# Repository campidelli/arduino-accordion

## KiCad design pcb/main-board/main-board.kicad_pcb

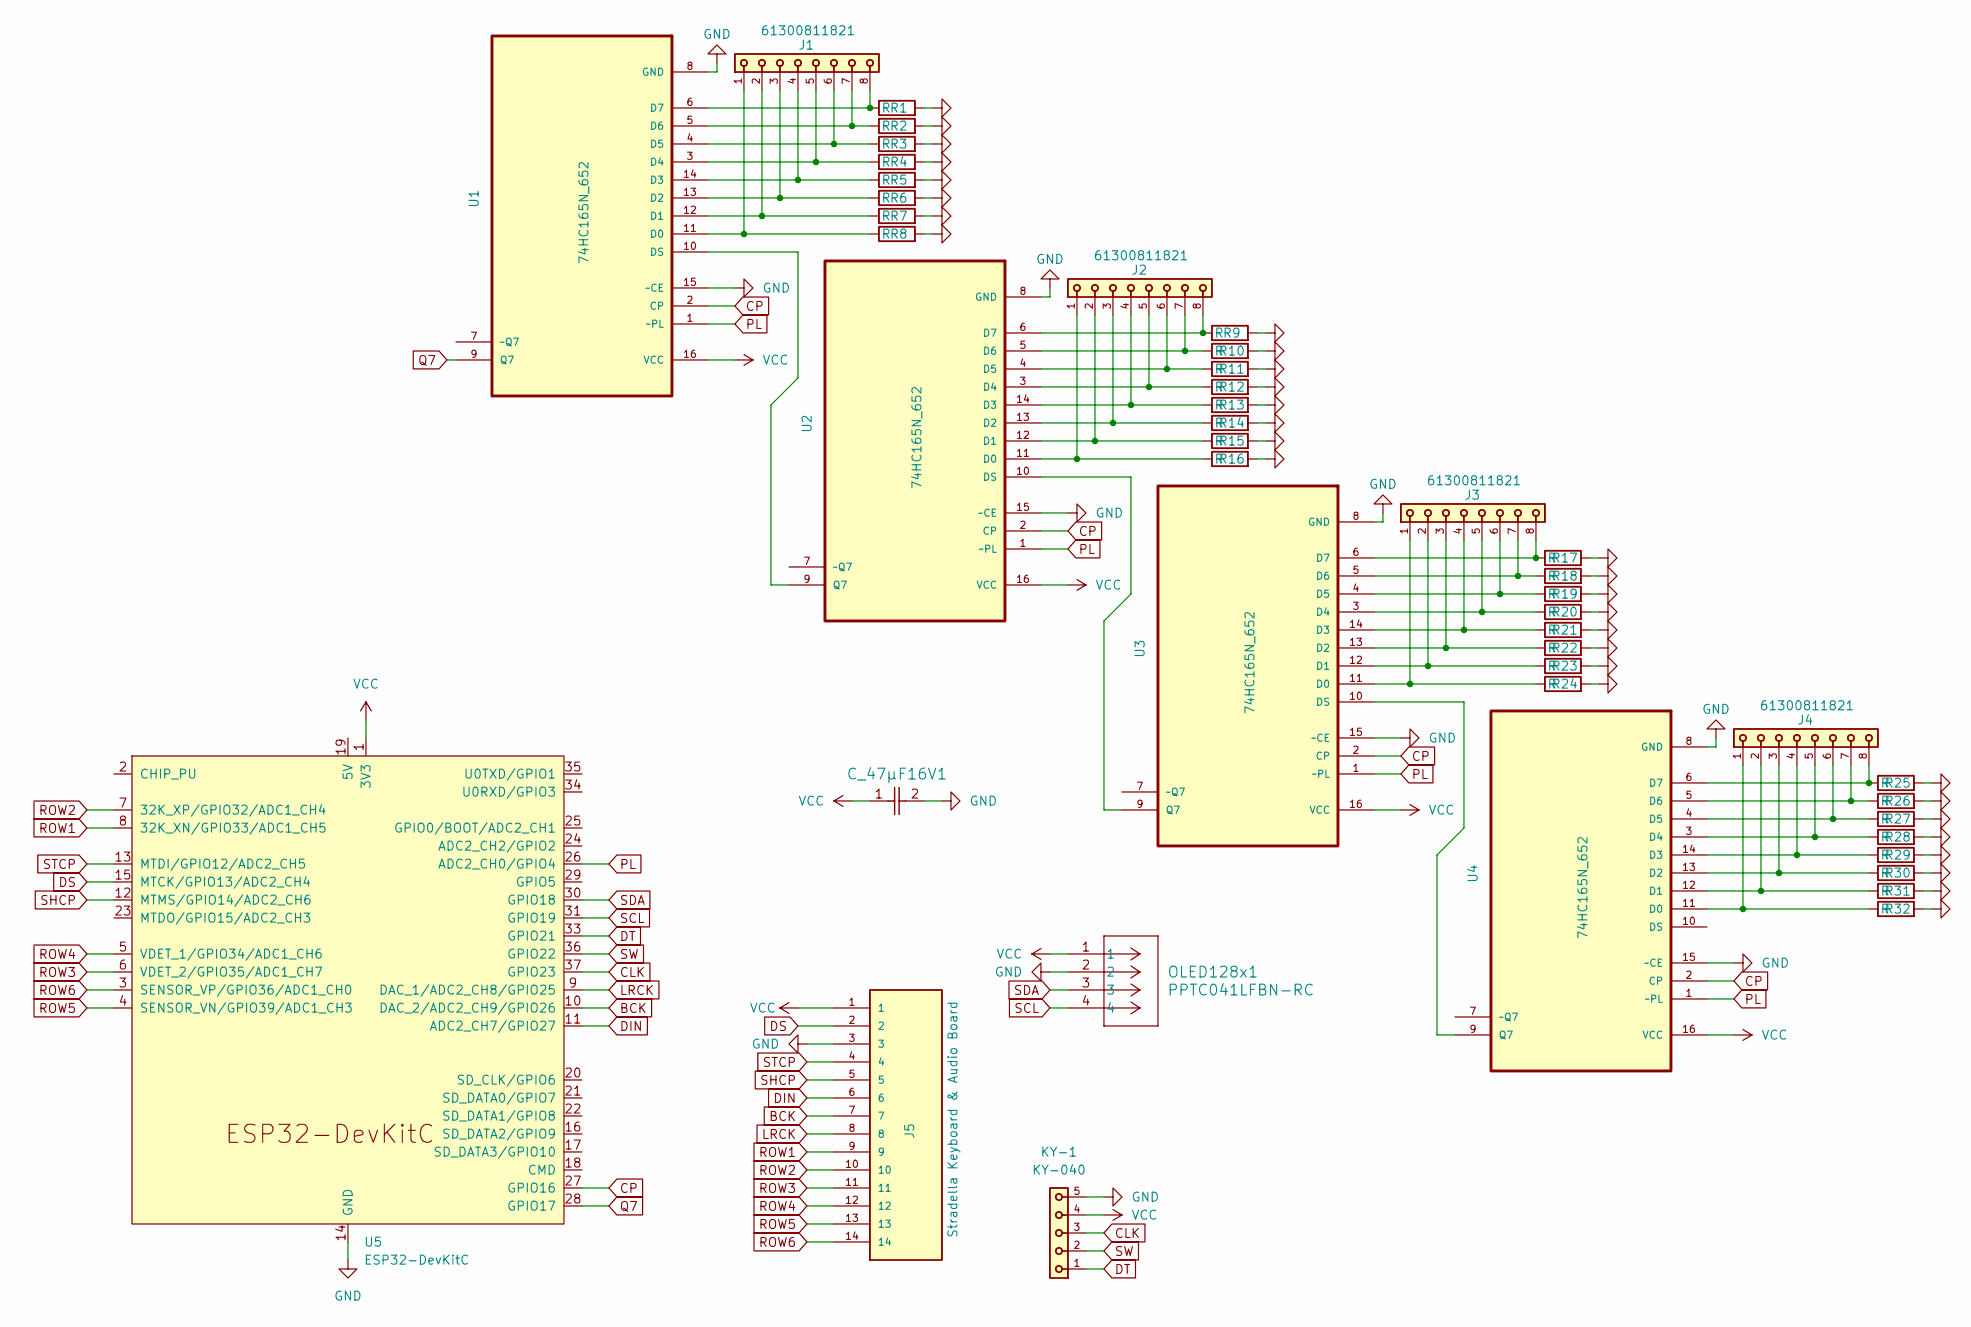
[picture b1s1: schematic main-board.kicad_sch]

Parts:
C_47µF16V1: ECA-1CHG470; EC-A_PAN
J1, J2, J3, J4: 61300811821; PART-NUMBER 61300811821
J5: Stradella Keyboard & Audio Board; TE_4-644694-4; PARTREV R
KY-1: KY-040; 61300511821; PART-NUMBER 61300511821
OLED128x1: PPTC041LFBN-RC; PPTC041LFBN_RC
R1, R2, R3, R4, R5, R6, R7, R8, R9, R10, R11, R12, R13, R14, R15, R16, R17, R18, R19, R20, R21, R22, R23, R24, R25, R26, R27, R28, R29, R30, R31, R32: R; R_Axial_DIN0204_L3.6mm_D1.6mm_P7.62mm_Horizontal
U1, U2, U3, U4: 74HC165N_652; DIP254P762X420-16; MPN 74HC165N,652
U5: ESP32-DevKitC

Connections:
BCK: J5.7, U5.10 (DAC_2/ADC2_CH9/GPIO26)
CLK: KY-1.3, U5.37 (GPIO23)
CP: U1.2 (CP), U2.2 (CP), U3.2 (CP), U4.2 (CP), U5.27 (GPIO16)
DIN: J5.6, U5.11 (ADC2_CH7/GPIO27)
DS: J5.2, U5.15 (MTCK/GPIO13/ADC2_CH4)
DT: KY-1.1, U5.33 (GPIO21)
GND: C_47µF16V1.2, J5.3, KY-1.5, OLED128x1.2, R1.2, R2.2, R3.2, R4.2, R5.2, R6.2, R7.2, R8.2, R9.2, R10.2, R11.2, R12.2, R13.2, R14.2, R15.2, R16.2, R17.2, R18.2, R19.2, R20.2, R21.2, R22.2, R23.2, R24.2, R25.2, R26.2, R27.2, R28.2, R29.2, R30.2, R31.2, R32.2, U1.8 (GND), U1.15 (~CE), U2.8 (GND), U2.15 (~CE), U3.8 (GND), U3.15 (~CE), U4.8 (GND), U4.15 (~CE), U5.14 (GND), U5.32 (GND), U5.38 (GND)
LRCK: J5.8, U5.9 (DAC_1/ADC2_CH8/GPIO25)
unnamed: J1.1, R8.1, U1.11 (D0)
unnamed: J1.2, R7.1, U1.12 (D1)
unnamed: J1.3, R6.1, U1.13 (D2)
unnamed: J1.4, R5.1, U1.14 (D3)
unnamed: J1.5, R4.1, U1.3 (D4)
unnamed: J1.6, R3.1, U1.4 (D5)
unnamed: J1.7, R2.1, U1.5 (D6)
unnamed: J1.8, R1.1, U1.6 (D7)
unnamed: U1.10 (DS), U2.9 (Q7)
unnamed: J2.1, R16.1, U2.11 (D0)
unnamed: J2.2, R15.1, U2.12 (D1)
unnamed: J2.3, R14.1, U2.13 (D2)
unnamed: J2.4, R13.1, U2.14 (D3)
unnamed: J2.5, R12.1, U2.3 (D4)
unnamed: J2.6, R11.1, U2.4 (D5)
unnamed: J2.7, R10.1, U2.5 (D6)
unnamed: J2.8, R9.1, U2.6 (D7)
unnamed: U2.10 (DS), U3.9 (Q7)
unnamed: J3.1, R24.1, U3.11 (D0)
unnamed: J3.2, R23.1, U3.12 (D1)
unnamed: J3.3, R22.1, U3.13 (D2)
unnamed: J3.4, R21.1, U3.14 (D3)
unnamed: J3.5, R20.1, U3.3 (D4)
unnamed: J3.6, R19.1, U3.4 (D5)
unnamed: J3.7, R18.1, U3.5 (D6)
unnamed: J3.8, R17.1, U3.6 (D7)
unnamed: U3.10 (DS), U4.9 (Q7)
unnamed: J4.1, R32.1, U4.11 (D0)
unnamed: J4.2, R31.1, U4.12 (D1)
unnamed: J4.3, R30.1, U4.13 (D2)
unnamed: J4.4, R29.1, U4.14 (D3)
unnamed: J4.5, R28.1, U4.3 (D4)
unnamed: J4.6, R27.1, U4.4 (D5)
unnamed: J4.7, R26.1, U4.5 (D6)
unnamed: J4.8, R25.1, U4.6 (D7)
PL: U1.1 (~PL), U2.1 (~PL), U3.1 (~PL), U4.1 (~PL), U5.26 (ADC2_CH0/GPIO4)
Q7: U1.9 (Q7), U5.28 (GPIO17)
ROW1: J5.9, U5.8 (32K_XN/GPIO33/ADC1_CH5)
ROW2: J5.10, U5.7 (32K_XP/GPIO32/ADC1_CH4)
ROW3: J5.11, U5.6 (VDET_2/GPIO35/ADC1_CH7)
ROW4: J5.12, U5.5 (VDET_1/GPIO34/ADC1_CH6)
ROW5: J5.13, U5.4 (SENSOR_VN/GPIO39/ADC1_CH3)
ROW6: J5.14, U5.3 (SENSOR_VP/GPIO36/ADC1_CH0)
SCL: OLED128x1.4, U5.31 (GPIO19)
SDA: OLED128x1.3, U5.30 (GPIO18)
SHCP: J5.5, U5.12 (MTMS/GPIO14/ADC2_CH6)
STCP: J5.4, U5.13 (MTDI/GPIO12/ADC2_CH5)
SW: KY-1.2, U5.36 (GPIO22)
VCC: C_47µF16V1.1, J5.1, KY-1.4, OLED128x1.1, U1.16 (VCC), U2.16 (VCC), U3.16 (VCC), U4.16 (VCC), U5.1 (3V3)

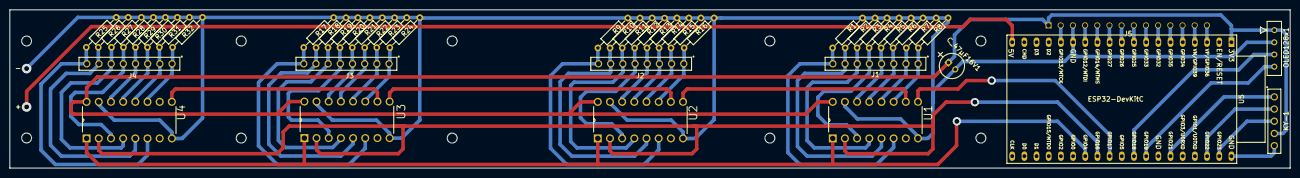
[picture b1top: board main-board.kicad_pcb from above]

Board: 2 copper layers, 267.0 x 33.0 mm, 45 parts (1 on the bottom side), 57 nets.

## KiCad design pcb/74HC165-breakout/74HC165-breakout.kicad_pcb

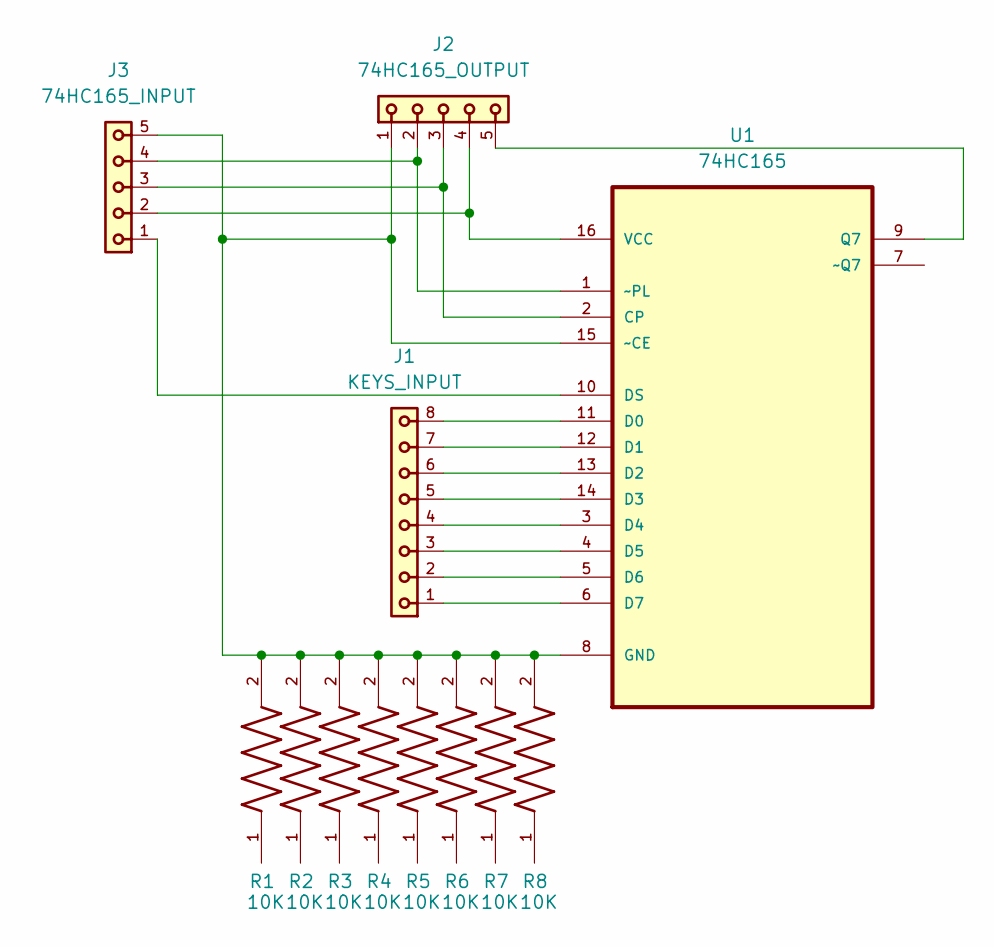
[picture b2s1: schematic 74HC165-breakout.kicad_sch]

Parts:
J1: KEYS_INPUT; 61300811821; PART-NUMBER 61300811821
J2: 74HC165_OUTPUT; 61300511821; PART-NUMBER 61300511821
J3: 74HC165_INPUT; 61300511821; PART-NUMBER 61300511821
R1, R2, R3, R4, R5, R6, R7, R8: 10K; RESAD1100W55L680D260; PARTREV 201304
U1: 74HC165; DIP254P762X420-16; MPN 74HC165N,652

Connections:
unnamed: J2.3, J3.3, U1.2 (CP)
unnamed: J1.8, U1.11 (D0)
unnamed: J1.7, U1.12 (D1)
unnamed: J1.6, U1.13 (D2)
unnamed: J1.5, U1.14 (D3)
unnamed: J1.4, U1.3 (D4)
unnamed: J1.3, U1.4 (D5)
unnamed: J1.2, U1.5 (D6)
unnamed: J1.1, U1.6 (D7)
unnamed: J3.1, U1.10 (DS)
unnamed: J2.1, J3.5, R1.2, R2.2, R3.2, R4.2, R5.2, R6.2, R7.2, R8.2, U1.8 (GND), U1.15 (~CE)
unnamed: J2.5, U1.9 (Q7)
unnamed: J2.4, J3.2, U1.16 (VCC)
unnamed: J2.2, J3.4, U1.1 (~PL)

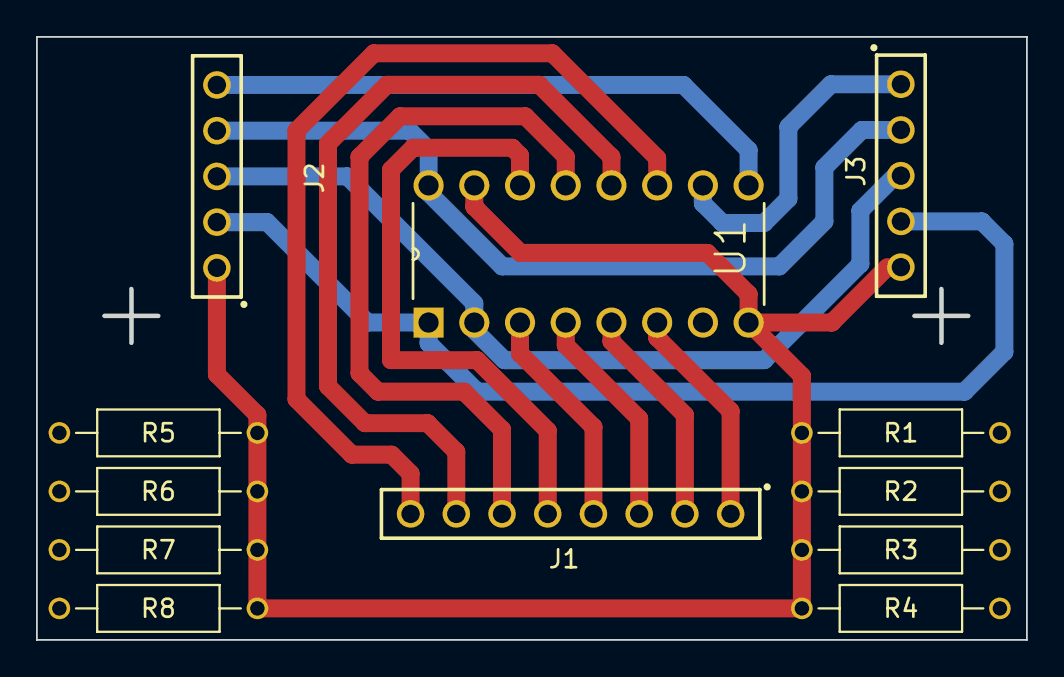
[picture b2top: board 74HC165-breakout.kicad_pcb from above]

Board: 2 copper layers, 54.8 x 33.3 mm, 12 parts (0 on the bottom side), 14 nets.

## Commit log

2024-08-30 Adding mozzi and Esp32SynchronizationContext
2024-09-01 Initial version. It doesn't compile.
2024-09-01 Fixing the python script to rename all ML .a files by adding a prefix lib to them.
2024-09-01 It is compiling now
2024-09-01 We no longer need the script to fix the lib names.
2024-09-02 Fixing the volume to prevent clipping.
2024-09-03 Improvements made, but it is hard to make it work well when using the Accordion and Voice classes.
2024-09-03 The library is powerful but the examples too specific.
2024-09-04 Experimenting with Low pass filter - not very useful for me.
2024-09-04 SoundFound trigger 'works', it needs a lot of refinements beyond my skills can handle.
2024-09-05 Adding more configuring options
2025-03-23 Blah
